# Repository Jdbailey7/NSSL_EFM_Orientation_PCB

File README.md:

# NSSL EFM Orientation PCB

In the paddle opposite the motor driver, an orientation sensor based on a simple IMU  
provides rough data on the instrument’s orientation over time. This allows analysis  
of pendulum motion and other movements of the full instrument package. The system is  
designed for easy sensor replacement, and all orientation data are logged to a  
microSD card.

See the [main instrument repo](https://github.com/LeemanGeophysicalLLC/NSSL_EFM_Instrument)
for documentation and the rest of the instrument.

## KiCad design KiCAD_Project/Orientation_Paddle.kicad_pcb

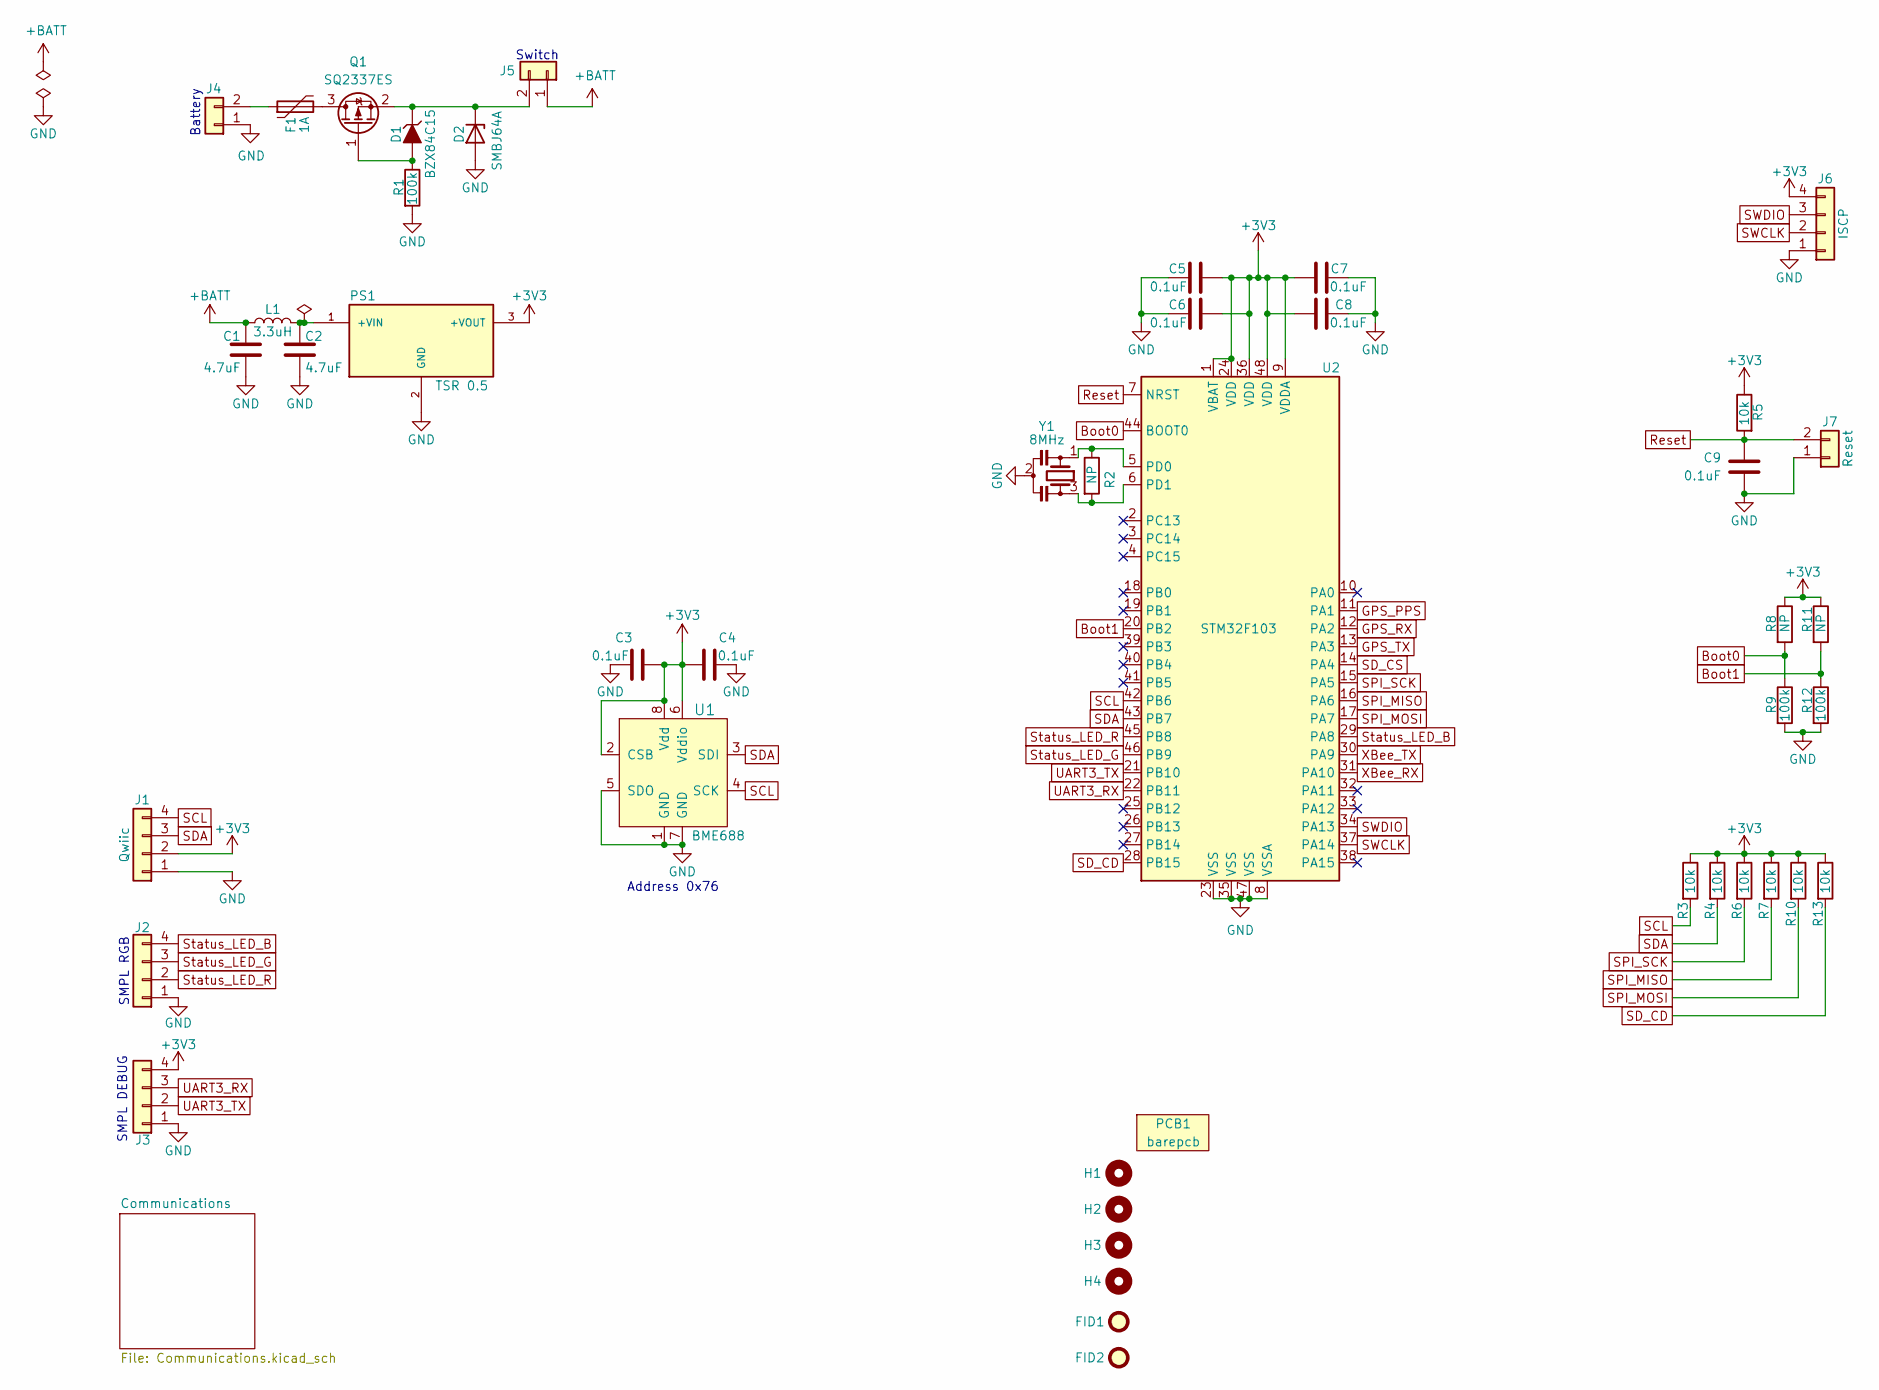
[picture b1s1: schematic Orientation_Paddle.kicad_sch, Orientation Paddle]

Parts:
C1, C2: 1-0000136
C3, C4, C5, C6, C7, C8, C9: 1-0000007
D1: 1-0001672
D2: 1-0001537
F1: 1-0001517
FID1, FID2: Fiducial_1mm_2mm; Fiducial_1mm_Mask2mm
H1, H2, H3, H4: Imperial6; MountingHole_imperial6
J1: 1-0001205
J2, J3: 1-0001156
J4, J5: NP_Conn_01x02_Relief; SolderWire_1x02_Relief
J6: NP_Conn_01x04; PinHeader_1x04_P2.54mm_Vertical
J7: NP_Conn_01x02; PinHeader_1x02_P2.54mm_Vertical
L1: 1-0000931
PCB1: barepcb
PS1: 1-0000727
Q1: 1-0001670
R1, R9, R12: 1-0000174
R2: 1-0000009
R3, R4, R5, R6, R7, R10, R13: 1-0000010
R8, R11: 1-0000006
U1: 1-0001471
U2: 1-0000207
Y1: 1-0000721

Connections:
+3V3: C3.2, C4.1, C5.1, C6.1, C7.1, C8.1, J1.2, J3.4, J6.4, PS1.3 (+VOUT), R3.1, R4.1, R5.1, R6.1, R7.1, R8.1, R10.1, R11.1, R13.1, U1.2 (CSB), U1.6 (Vddio), U1.8 (Vdd), U2.1 (VBAT), U2.9 (VDDA), U2.24 (VDD), U2.36 (VDD), U2.48 (VDD); also elsewhere on the board
+BATT: C1.1, J5.1, L1.1
Boot0: R8.2, R9.1, U2.44 (BOOT0)
Boot1: R11.2, R12.1, U2.20 (PB2)
GND: C1.2, C2.2, C3.1, C4.2, C5.2, C6.2, C7.2, C8.2, C9.2, D2.2 (A), J1.1, J2.1, J3.1, J4.1, J6.1, J7.1, PS1.2 (GND), R1.2, R9.2, R12.2, U1.1 (GND), U1.5 (SDO), U1.7 (GND), U2.8 (VSSA), U2.23 (VSS), U2.35 (VSS), U2.47 (VSS), Y1.2; also elsewhere on the board
GPS_PPS: U2.11 (PA1); also elsewhere on the board
GPS_RX: U2.12 (PA2); also elsewhere on the board
GPS_TX: U2.13 (PA3); also elsewhere on the board
unnamed: D1.1 (A), Q1.1 (G), R1.1
unnamed: D1.3 (K), D2.1 (K), J5.2, Q1.2 (S)
unnamed: F1.1, J4.2
unnamed: C2.1, L1.2, PS1.1 (+VIN)
unnamed: F1.2, Q1.3 (D)
unnamed: R2.1, U2.5 (PD0), Y1.1
unnamed: R2.2, U2.6 (PD1), Y1.3
Reset: C9.1, J7.2, R5.2, U2.7 (NRST); also elsewhere on the board
SCL: J1.4, R3.2, U1.4 (SCK), U2.42 (PB6); also elsewhere on the board
SDA: J1.3, R4.2, U1.3 (SDI), U2.43 (PB7); also elsewhere on the board
SD_CD: R13.2, U2.28 (PB15); also elsewhere on the board
SD_CS: U2.14 (PA4); also elsewhere on the board
SPI_MISO: R7.2, U2.16 (PA6); also elsewhere on the board
SPI_MOSI: R10.2, U2.17 (PA7); also elsewhere on the board
SPI_SCK: R6.2, U2.15 (PA5); also elsewhere on the board
SWCLK: J6.2, U2.37 (PA14)
SWDIO: J6.3, U2.34 (PA13)
Status_LED_B: J2.4, U2.29 (PA8)
Status_LED_G: J2.3, U2.46 (PB9)
Status_LED_R: J2.2, U2.45 (PB8)
UART3_RX: J3.3, U2.22 (PB11)
UART3_TX: J3.2, U2.21 (PB10)
XBee_RX: U2.31 (PA10); also elsewhere on the board
XBee_TX: U2.30 (PA9); also elsewhere on the board

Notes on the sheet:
Battery
Address 0x76
SMPL DEBUG
Switch
SMPL RGB

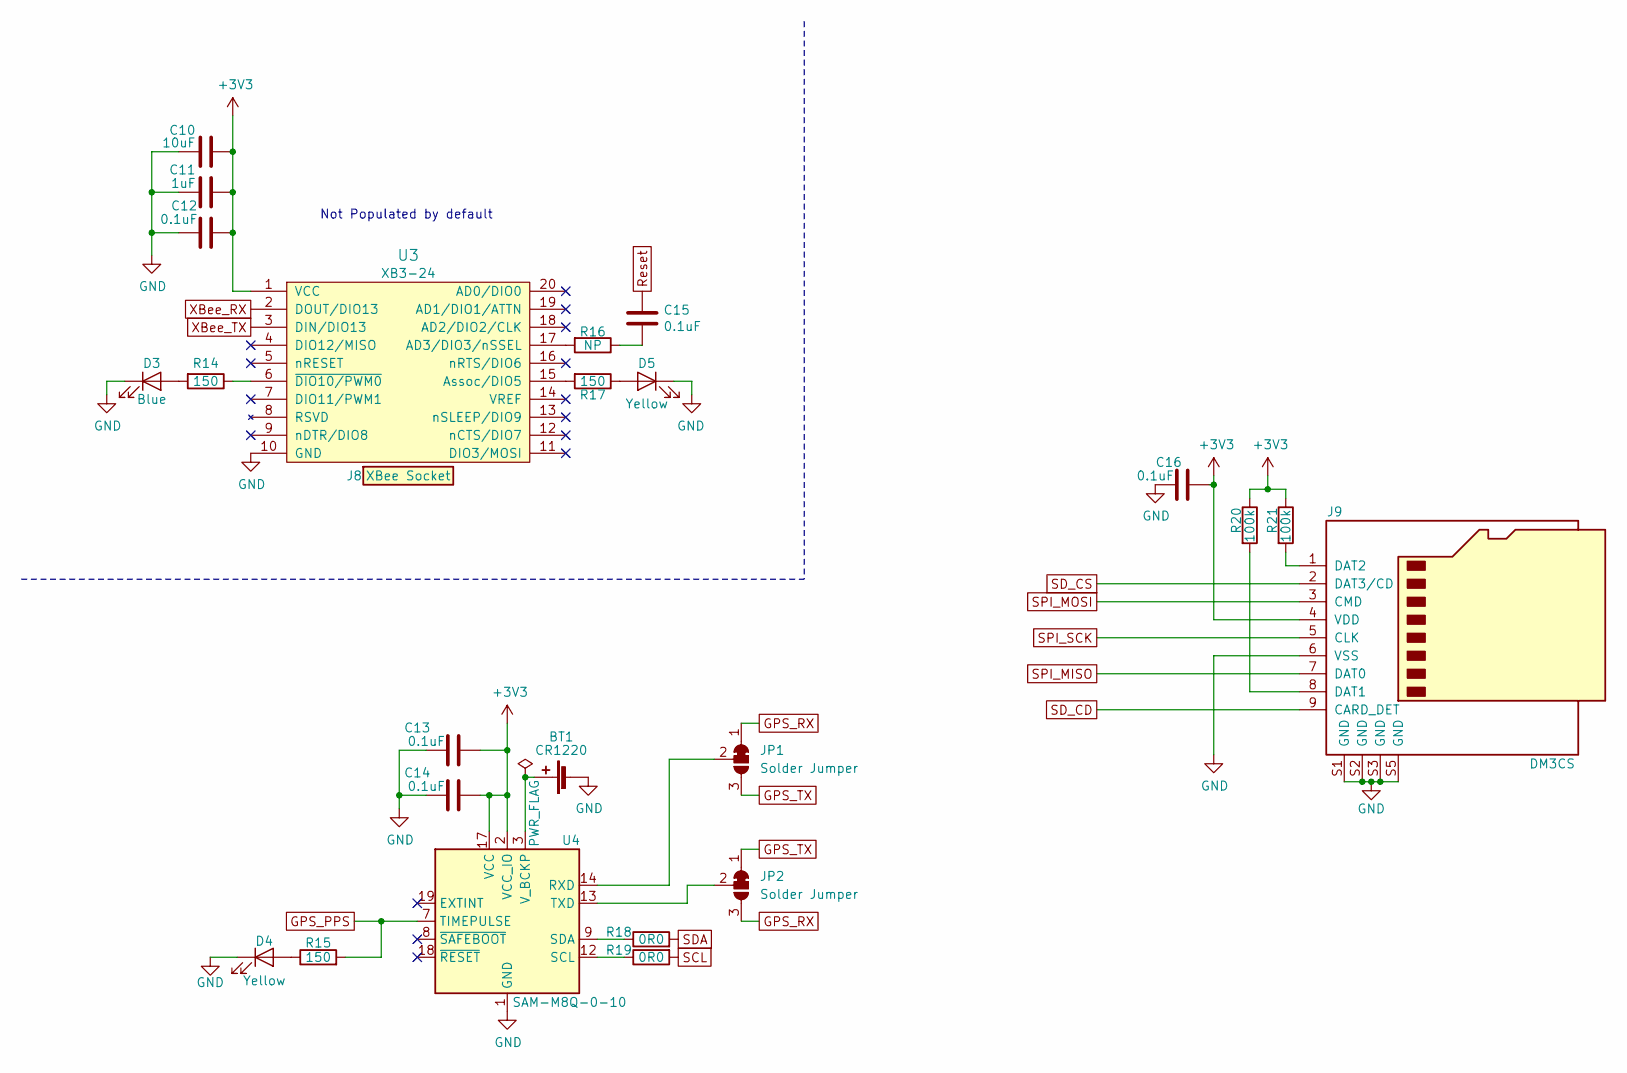
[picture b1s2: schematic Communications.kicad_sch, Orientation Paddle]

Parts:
BT1: 1-0000246
C10: 1-0000075
C11: 1-0000018
C12, C13, C14, C15, C16: 1-0000007
D3: 1-0000599
D4, D5: 1-0000601
J8: 1-0000050
J9: 1-0000190
JP1, JP2: SolderJumper_3_Bridged12; SolderJumper-3_P1.3mm_Bridged12_RoundedPad1.0x1.5mm
R14, R15, R17: 1-0000008
R16, R18, R19: 1-0000006
R20, R21: 1-0000174
U3: 1-0000785
U4: 1-0000446

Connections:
+3V3: C10.1, C11.1, C12.1, C13.1, C14.1, C16.2, J9.4 (VDD), R20.1, R21.1, U3.1 (VCC), U4.2 (VCC_IO), U4.17 (VCC); also elsewhere on the board
GND: BT1.2 (-), C10.2, C11.2, C12.2, C13.2, C14.2, C16.1, D3.1 (K), D4.1 (K), D5.1 (K), J9.6 (VSS), J9.S1 (GND), J9.S2 (GND), J9.S3 (GND), J9.S5 (GND), U3.10 (GND), U4.1 (GND), U4.4 (GND), U4.5 (GND), U4.6 (GND), U4.10 (GND), U4.11 (GND), U4.15 (GND), U4.16 (GND), U4.20 (GND); also elsewhere on the board
GPS_PPS: R15.2, U4.7 (TIMEPULSE); also elsewhere on the board
GPS_RX: JP1.1 (A), JP2.3 (B); also elsewhere on the board
GPS_TX: JP1.3 (B), JP2.1 (A); also elsewhere on the board
unnamed: BT1.1 (+), U4.3 (V_BCKP)
unnamed: C15.2, R16.1
unnamed: D3.2 (A), R14.2
unnamed: D4.2 (A), R15.1
unnamed: D5.2 (A), R17.1
unnamed: J9.8 (DAT1), R20.2
unnamed: J9.1 (DAT2), R21.2
unnamed: JP1.2 (C), U4.14 (RXD)
unnamed: JP2.2 (C), U4.13 (TXD)
unnamed: R16.2, U3.17 (AD3/DIO3/nSSEL)
unnamed: R17.2, U3.15 (Assoc/DIO5)
unnamed: R14.1, U3.6 (~DIO10/PWM0)
unnamed: R19.1, U4.12 (SCL)
unnamed: R18.1, U4.9 (SDA)
Reset: C15.1; also elsewhere on the board
SCL: R19.2; also elsewhere on the board
SDA: R18.2; also elsewhere on the board
SD_CD: J9.9 (CARD_DET); also elsewhere on the board
SD_CS: J9.2 (DAT3/CD); also elsewhere on the board
SPI_MISO: J9.7 (DAT0); also elsewhere on the board
SPI_MOSI: J9.3 (CMD); also elsewhere on the board
SPI_SCK: J9.5 (CLK); also elsewhere on the board
XBee_RX: U3.2 (DOUT/DIO13); also elsewhere on the board
XBee_TX: U3.3 (DIN/DIO13); also elsewhere on the board

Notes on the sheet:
Not Populated by default

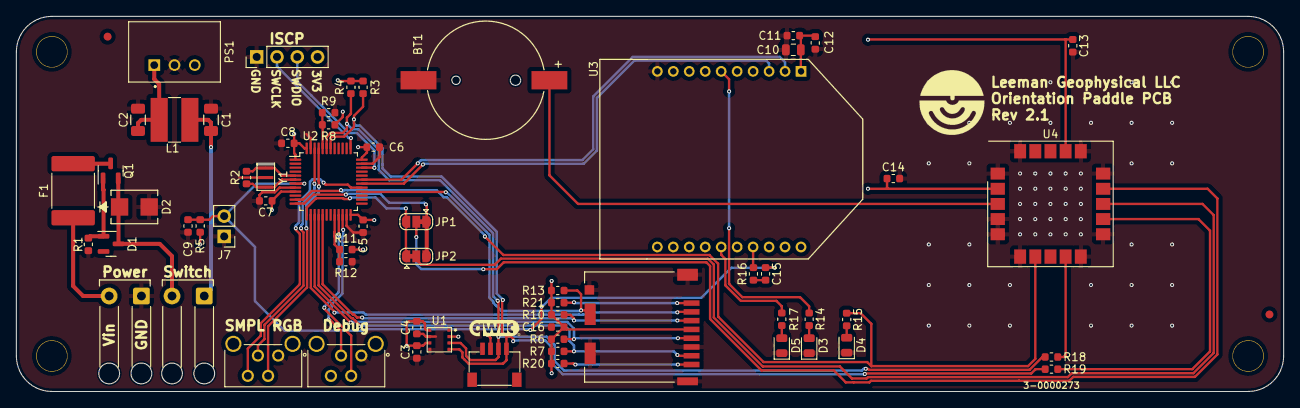
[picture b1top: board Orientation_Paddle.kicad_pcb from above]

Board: 2 copper layers, 158.7 x 47.0 mm, 70 parts (0 on the bottom side), 46 nets.

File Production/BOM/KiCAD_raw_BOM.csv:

"Reference","Value","Internal Part Number","PValue","Populated"
"BT1","1-0000246","1-0000246","CR1220","1"
"C1","1-0000136","1-0000136","4.7uF","1"
"C2","1-0000136","1-0000136","4.7uF","1"
"C3","1-0000007","1-0000007","0.1uF","0"
"C4","1-0000007","1-0000007","0.1uF","0"
"C5","1-0000007","1-0000007","0.1uF","1"
"C6","1-0000007","1-0000007","0.1uF","1"
"C7","1-0000007","1-0000007","0.1uF","1"
"C8","1-0000007","1-0000007","0.1uF","1"
"C9","1-0000007","1-0000007","0.1uF","1"
"C10","1-0000075","1-0000075","10uF","0"
"C11","1-0000018","1-0000018","1uF","0"
"C12","1-0000007","1-0000007","0.1uF","0"
"C13","1-0000007","1-0000007","0.1uF","1"
"C14","1-0000007","1-0000007","0.1uF","1"
"C15","1-0000007","1-0000007","0.1uF","0"
"C16","1-0000007","1-0000007","0.1uF","1"
"D1","1-0001672","1-0001672","BZX84C15","1"
"D2","1-0001537","1-0001537","SMBJ64A","1"
"D3","1-0000599","1-0000599","Blue","0"
"D4","1-0000601","1-0000601","Yellow","0"
"F1","1-0001517","1-0001517","1A","1"
"FID1","Fiducial_1mm_2mm","0-0000000","Fiducial","0"
"FID2","Fiducial_1mm_2mm","0-0000000","Fiducial","0"
"J1","1-0001205","1-0001205","Qwiic","1"
"J2","1-0001156","1-0001156","4 Pos","1"
"J3","1-0001156","1-0001156","4 Pos","1"
"J4","NP_Conn_01x02_Relief","0-0000000","NP_Conn_01x02","0"
"J5","NP_Conn_01x02_Relief","0-0000000","NP_Conn_01x02","0"
"J6","NP_Conn_01x04","0-0000000","ISCP","0"
"J7","NP_Conn_01x02","0-0000000","Reset","0"
"J8","1-0000050","1-0000050","XBee Socket","0"
"J9","1-0000190","1-0000190","DM3CS","1"
"L1","1-0000931","1-0000931","3.3uH","1"
"PCB1","barepcb","3-0000267","Bare PCB","1"
"PS1","1-0000727","1-0000727","TSR 0.5","1"
"Q1","1-0001670","1-0001670","SQ2337ES","1"
"R1","1-0000174","1-0000174","100k","1"
"R2","1-0000009","1-0000009","NP","0"
"R3","1-0000010","1-0000010","10k","1"
"R4","1-0000010","1-0000010","10k","1"
"R5","1-0000010","1-0000010","10k","1"
"R6","1-0000010","1-0000010","10k","1"
"R7","1-0000010","1-0000010","10k","1"
"R8","1-0000006","1-0000006","NP","0"
"R9","1-0000174","1-0000174","100k","1"
"R10","1-0000010","1-0000010","10k","1"
"R11","1-0000006","1-0000006","NP","0"
"R12","1-0000174","1-0000174","100k","1"
"R13","1-0000010","1-0000010","10k","1"
"R14","1-0000008","1-0000008","150","0"
"R15","1-0000006","1-0000006","NP","0"
"R16","1-0000008","1-0000008","150","0"
"R17","1-0000174","1-0000174","100k","1"
"R18","1-0000174","1-0000174","100k","1"
"U1","1-0001471","1-0001471","BME688","0"
"U2","1-0000207","1-0000207","STM32F103","1"
"U3","1-0000446","1-0000446","SAM-M8Q-0-10","1"
"U4","1-0000785","1-0000785","XB3-24","0"
"Y1","1-0000721","1-0000721","8MHz","1"

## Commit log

2025-06-02 Version 1.0 as built
2025-06-03 Rev 2.0 Changes: Fixed the following issues, - Issue #7 (Added RP Protection) - Issue #6 (Removed old encoder and sense connections) - Issue #5 (Solidified Serial connections by removing jumpers) - I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
2025-06-03 Make Rev 2.0 production files
2025-07-03 Fixed Issues #9, Issue #10 (Rev2.1)
2025-07-04 Add serial jumpers for GPS and make production files for Rev 2.1
